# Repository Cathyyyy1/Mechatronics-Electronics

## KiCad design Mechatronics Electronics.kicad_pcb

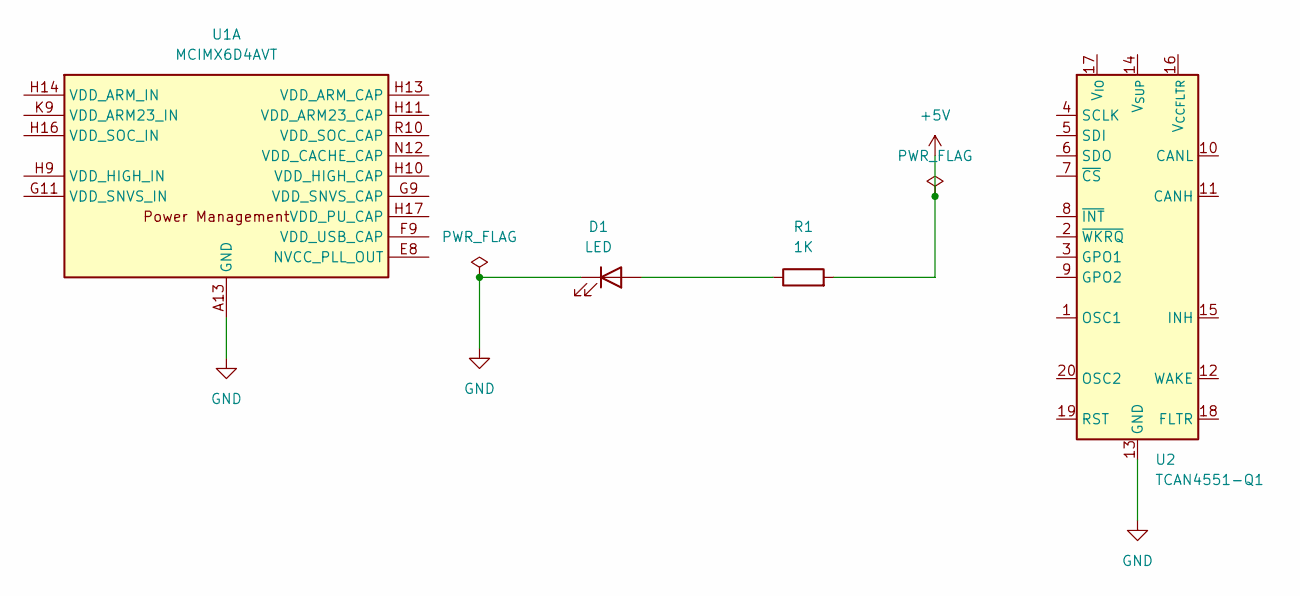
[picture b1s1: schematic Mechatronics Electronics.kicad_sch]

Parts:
D1: LED; LED_miniPLCC_2315
R1: 1K; C_0603_1608Metric
U1: MCIMX6D4AVT; BGA-624_21x21mm_Layout25x25_P0.8mm
U2: TCAN4551-Q1

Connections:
+5V: R1.2
GND: D1.1 (K), U1.A4 (GND), U1.A8 (GND), U1.A13 (GND), U1.A25 (GND), U1.AA7 (GND), U1.AA10 (GND), U1.AA13 (GND), U1.AA16 (GND), U1.AA19 (GND), U1.AA22 (GND), U1.AB3 (GND), U1.AB24 (GND), U1.AD4 (GND), U1.AD7 (GND), U1.AD10 (GND), U1.AD13 (GND), U1.AD16 (GND), U1.AD19 (GND), U1.AD22 (GND), U1.AE1 (GND), U1.AE25 (GND), U1.B4 (GND), U1.C1 (GND), U1.C4 (GND), U1.C6 (GND), U1.C10 (GND), U1.D3 (GND), U1.D6 (GND), U1.D8 (GND), U1.E5 (GND), U1.E6 (GND), U1.E7 (GND), U1.F5 (GND), U1.F6 (GND), U1.F7 (GND), U1.F8 (GND), U1.G3 (GND), U1.G10 (GND), U1.G19 (GND), U1.H8 (GND), U1.H12 (GND), U1.H15 (GND), U1.H18 (GND), U1.J2 (GND), U1.J8 (GND), U1.J12 (GND), U1.J15 (GND), U1.J18 (GND), U1.K8 (GND), U1.K10 (GND), U1.K12 (GND), U1.K15 (GND), U1.K18 (GND), U1.L2 (GND), U1.L5 (GND), U1.L8 (GND), U1.L10 (GND), U1.L12 (GND), U1.L15 (GND), U1.L18 (GND), U1.M8 (GND), U1.M10 (GND), U1.M12 (GND), U1.M15 (GND), U1.M18 (GND), U1.N8 (GND), U1.N10 (GND), U1.N15 (GND), U1.N18 (GND), U1.P8 (GND), U1.P10 (GND), U1.P12 (GND), U1.P15 (GND), U1.P18 (GND), U1.R8 (GND), U1.R12 (GND), U1.R15 (GND), U1.R17 (GND), U1.T8 (GND), U1.T11 (GND), U1.T12 (GND), U1.T15 (GND), U1.T17 (GND), U1.T19 (GND), U1.U8 (GND), U1.U11 (GND), U1.U12 (GND), U1.U15 (GND), U1.U17 (GND), U1.U19 (GND), U1.V8 (GND), U1.V19 (GND), U1.W3 (GND), U1.W7 (GND), U1.W8 (GND), U1.W9 (GND), U1.W10 (GND), U1.W11 (GND), U1.W12 (GND), U1.W13 (GND), U1.W15 (GND), U1.W16 (GND), U1.W17 (GND), U1.W18 (GND), U1.W19 (GND), U1.Y5 (GND), U1.Y24 (GND), U2.13 (GND), U2.21 (GND)
unnamed: D1.2 (A), R1.1
unnamed: U1.H11 (VDD_ARM23_CAP), U1.J11 (VDD_ARM23_CAP), U1.K11 (VDD_ARM23_CAP), U1.L11 (VDD_ARM23_CAP), U1.M11 (VDD_ARM23_CAP), U1.N11 (VDD_ARM23_CAP), U1.P11 (VDD_ARM23_CAP), U1.R11 (VDD_ARM23_CAP)
unnamed: U1.K9 (VDD_ARM23_IN), U1.L9 (VDD_ARM23_IN), U1.M9 (VDD_ARM23_IN), U1.N9 (VDD_ARM23_IN), U1.P9 (VDD_ARM23_IN), U1.R9 (VDD_ARM23_IN), U1.T9 (VDD_ARM23_IN), U1.U9 (VDD_ARM23_IN)
unnamed: U1.H13 (VDD_ARM_CAP), U1.J13 (VDD_ARM_CAP), U1.K13 (VDD_ARM_CAP), U1.L13 (VDD_ARM_CAP), U1.M13 (VDD_ARM_CAP), U1.N13 (VDD_ARM_CAP), U1.P13 (VDD_ARM_CAP), U1.R13 (VDD_ARM_CAP)
unnamed: U1.H14 (VDD_ARM_IN), U1.J14 (VDD_ARM_IN), U1.K14 (VDD_ARM_IN), U1.L14 (VDD_ARM_IN), U1.M14 (VDD_ARM_IN), U1.N14 (VDD_ARM_IN), U1.P14 (VDD_ARM_IN), U1.R14 (VDD_ARM_IN)
unnamed: U1.H10 (VDD_HIGH_CAP), U1.J10 (VDD_HIGH_CAP)
unnamed: U1.H9 (VDD_HIGH_IN), U1.J9 (VDD_HIGH_IN)
unnamed: U1.H17 (VDD_PU_CAP), U1.J17 (VDD_PU_CAP), U1.K17 (VDD_PU_CAP), U1.L17 (VDD_PU_CAP), U1.M17 (VDD_PU_CAP), U1.N17 (VDD_PU_CAP), U1.P17 (VDD_PU_CAP)
unnamed: U1.R10 (VDD_SOC_CAP), U1.T10 (VDD_SOC_CAP), U1.T13 (VDD_SOC_CAP), U1.T14 (VDD_SOC_CAP), U1.U10 (VDD_SOC_CAP), U1.U13 (VDD_SOC_CAP), U1.U14 (VDD_SOC_CAP)
unnamed: U1.H16 (VDD_SOC_IN), U1.J16 (VDD_SOC_IN), U1.K16 (VDD_SOC_IN), U1.L16 (VDD_SOC_IN), U1.M16 (VDD_SOC_IN), U1.N16 (VDD_SOC_IN), U1.P16 (VDD_SOC_IN), U1.R16 (VDD_SOC_IN), U1.T16 (VDD_SOC_IN), U1.U16 (VDD_SOC_IN)

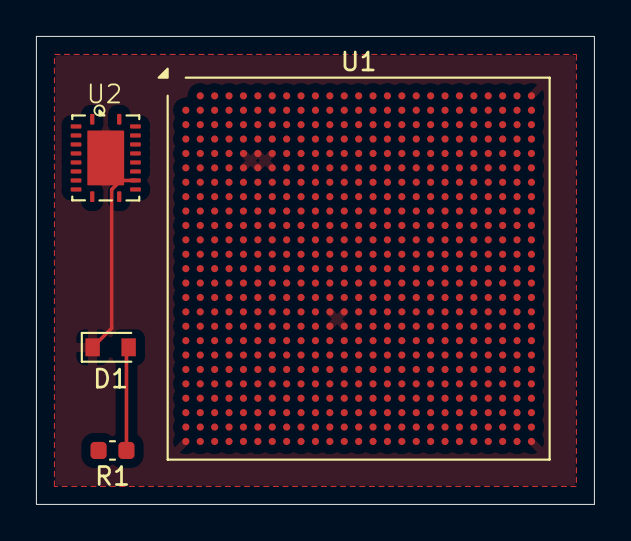
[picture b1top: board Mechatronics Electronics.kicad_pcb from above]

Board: 2 copper layers, 31.0 x 26.0 mm, 4 parts (0 on the bottom side), 11 nets.

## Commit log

2025-09-28 Add Mechatronics Electronics project files
2025-09-28 Added TCAN4551-Q1 custom footprint/symbol and applied BGA microvia DRC rule
    - Created and linked custom symbol + footprint for TCAN4551-Q1
    - Added KiCad default MCIMX6D4AVT symbol
    - Defined BGA_Area rule with microvia geometry:
    * Min annular width: 2 mil
    * Min via diameter: 8 mil
    * Min via hole size: 4 mil
2025-09-28 Add TCAN_Library as submodule at libs/TCAN_Library
2025-09-28 Point project libs to TCAN_Library submodule via paths
2025-09-28 Remove backups/locks/local prefs from repo
